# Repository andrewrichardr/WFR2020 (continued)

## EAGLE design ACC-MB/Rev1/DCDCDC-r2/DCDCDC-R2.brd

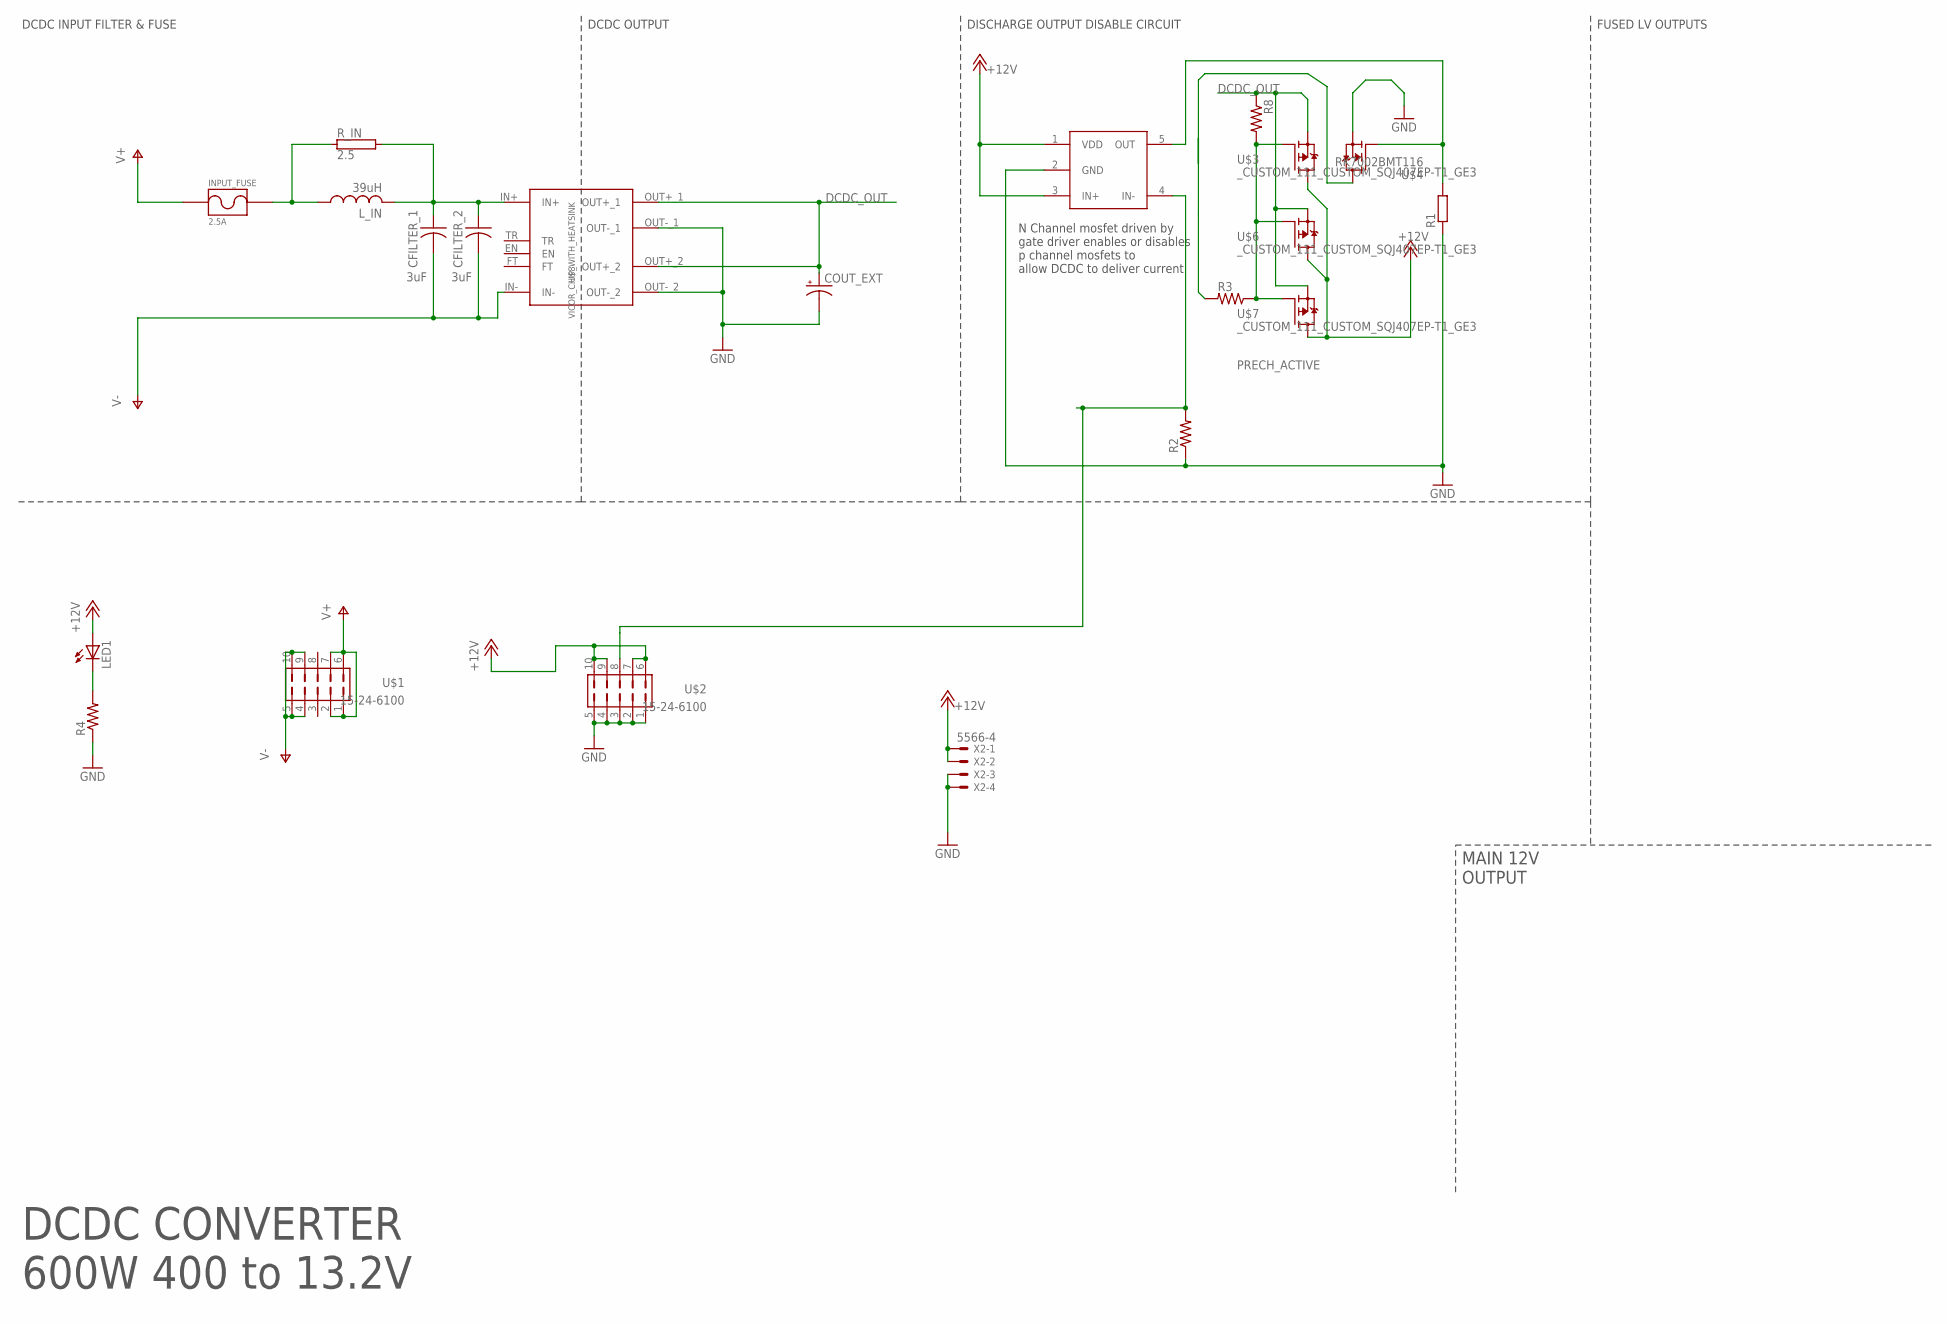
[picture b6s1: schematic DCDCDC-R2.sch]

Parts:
CFILTER_1, CFILTER_2: 3uF; CERALINK_FA3
COUT_EXT: CPOL-USE7.5-16; E7,5-16
INPUT_FUSE: 2.5A; _CUSTOM_PARTS_LF_885
LED1: LED3MM
L_IN: 39uH; L_1510_NONSTANDARD
R1: R-EU_R0805; R0805
R2, R3, R4, R8: R-US_R0805; R0805
R_IN: 2.5; TO-247-2V
U$1, U$2: 15-24-6100
U$3, U$6, U$7: _CUSTOM_111_CUSTOM_SQJ407EP-T1_GE3; _CUSTOM_111_CUSTOM_TRANS_SIRA90DP-T1-GE3
U$4: RK7002BMT116; SOT23
U$5: UCC27511AQDBVRQ1; SOT23-5L
U$8: VICOR_CHIP_WITH_HEATSINK; VICOR_CHIP_HEATSINK
X2: 5566-4

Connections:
+12V: LED1.A, U$2.6, U$2.7, U$2.9, U$2.10, U$3.5 (D), U$5.1 (VDD), U$5.3 (IN+), U$6.5 (D), U$7.5 (D), X2.1, X2.2
DCDC_OUT: COUT_EXT.+, R8.1, U$3.1 (S), U$3.2 (S), U$3.3 (S), U$6.1 (S), U$6.2 (S), U$6.3 (S), U$7.1 (S), U$7.2 (S), U$7.3 (S), U$8.OUT+_1, U$8.OUT+_2
GND: COUT_EXT.-, R1.1, R2.1, R4.1, U$2.1, U$2.2, U$2.3, U$2.4, U$2.5, U$4.2 (S), U$5.2 (GND), U$8.OUT-_1, U$8.OUT-_2, X2.3, X2.4
unnamed: R3.1, R8.2, U$3.4 (G), U$6.4 (G), U$7.4 (G)
unnamed: R1.2, U$4.1 (G), U$5.5 (OUT)
unnamed: CFILTER_1.P$1 (1), CFILTER_2.P$1 (1), L_IN.P$2 (2), R_IN.2, U$8.IN+
unnamed: R3.2, U$4.3 (D)
unnamed: LED1.K (C), R4.2
PRECH_ACTIVE: R2.2, U$2.8, U$5.4 (IN-)
V+: INPUT_FUSE.P$1, U$1.1, U$1.2, U$1.6, U$1.7
V+_FUSED: INPUT_FUSE.P$2, L_IN.P$1 (1), R_IN.1
V-: CFILTER_1.P$2 (2), CFILTER_2.P$2 (2), U$1.4, U$1.5, U$1.9, U$1.10, U$8.IN-

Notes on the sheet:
DCDC CONVERTER 600W 400 to 13.2V
DISCHARGE OUTPUT DISABLE CIRCUIT
FUSED LV OUTPUTS
MAIN 12V OUTPUT
DCDC OUTPUT
DCDC INPUT FILTER & FUSE
N Channel mosfet driven by gate driver enables or disables p channel mosfets to allow DCDC to deliver current

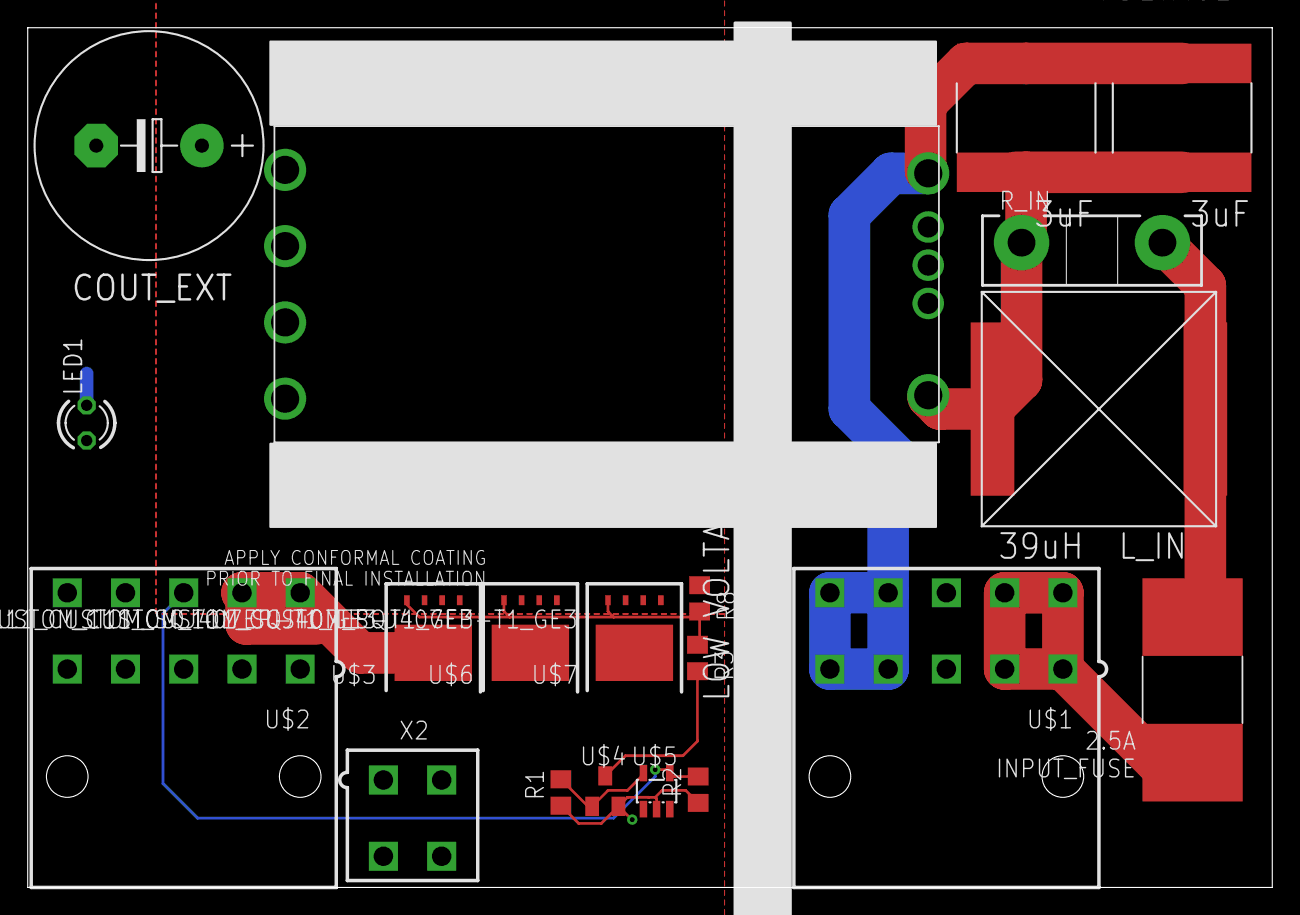
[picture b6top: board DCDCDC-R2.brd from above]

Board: 2 copper layers, 89.8 x 62.0 mm, 23 parts (1 on the bottom side), 12 nets.

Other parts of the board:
U$9, U$10: 7792

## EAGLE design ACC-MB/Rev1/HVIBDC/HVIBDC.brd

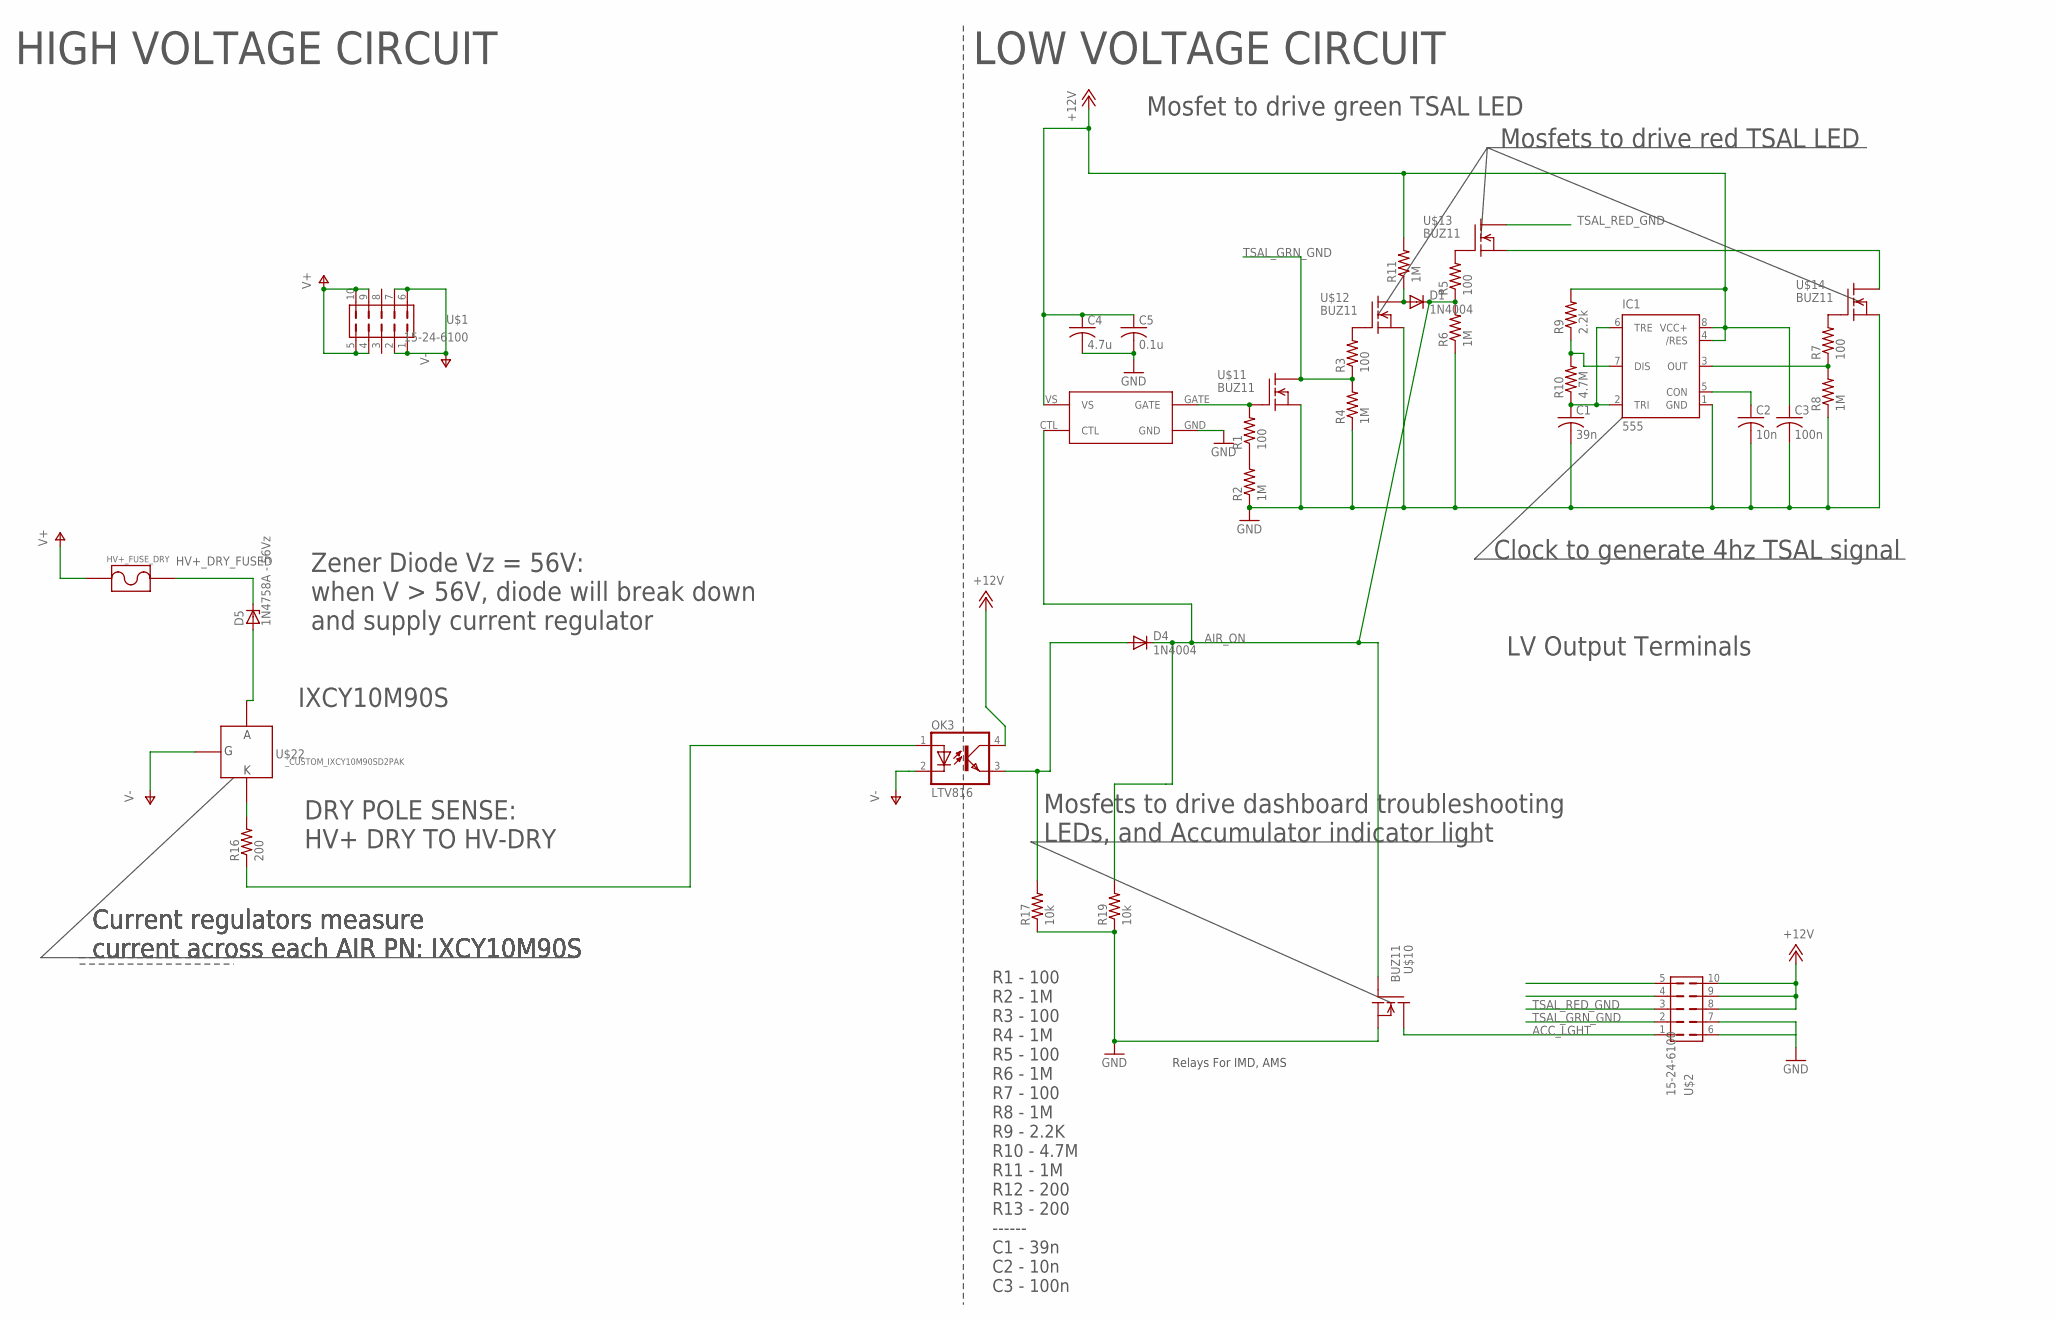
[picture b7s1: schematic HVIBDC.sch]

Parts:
C1: 39n; C0805
C2: 10n; C0805
C3: 100n; C0805
C4: 4.7u; C0805
C5: 0.1u; C0805
D1, D4: 1N4004; DO41-10
D5: 1N4758A - 56Vz; ZDIO12.5
HV+_FUSE_DRY: _CUSTOM_PARTS_LF_885
IC1: 555; DIP08
OK3: LTV816; DIL04
R1, R3, R5, R7: 100; R0805
R2, R4, R6, R8, R11: 1M; R0805
R9: 2.2k; R0805
R10: 4.7M; R0805
R16: 200; R2010
R17, R19: 10k; R0805
U$1, U$2: 15-24-6100
U$10, U$11, U$12, U$13, U$14: BUZ11; TO220
U$15: MIC4417; PDM_2019_REVB_MIC4416YM4-TR
U$22: _CUSTOM_IXCY10M90SD2PAK; TO228P991X238-3

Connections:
+12V: C3.1, C4.1, C5.1, IC1.4 (/RES), IC1.8 (VCC+), OK3.4 (COL), R9.2, R11.2, U$2.8, U$2.9, U$2.10, U$15.VS
ACC_LGHT: U$2.1, U$10.2 (D)
AIR_ON: D1.C, D4.C, R5.1, R6.2, R19.2, U$10.1 (G), U$15.CTL
GND: C1.2, C2.2, C3.2, C4.2, C5.2, IC1.1 (GND), R2.1, R4.1, R6.1, R8.1, R17.1, R19.1, U$2.7, U$10.3 (S), U$11.3 (S), U$12.3 (S), U$14.3 (S), U$15.GND
HV+_DRY_FUSED: D5.C, HV+_FUSE_DRY.P$1
unnamed: R1.1, R2.2
unnamed: R1.2, U$11.1 (G), U$15.GATE
unnamed: R3.2, U$12.1 (G)
unnamed: C2.1, IC1.5 (CON)
unnamed: IC1.7 (DIS), R9.1, R10.2
unnamed: R5.2, U$13.1 (G)
unnamed: R7.2, U$14.1 (G)
unnamed: IC1.3 (OUT), R7.1, R8.2
unnamed: C1.1, IC1.2 (TRI), IC1.6 (TRE), R10.1
unnamed: U$13.3 (S), U$14.2 (D)
unnamed: D4.A, OK3.3 (EMIT), R17.2
unnamed: D1.A, R11.1, U$12.2 (D)
unnamed: R16.2, U$22.2 (K)
unnamed: D5.A, U$22.3 (A)
unnamed: OK3.1 (A), R16.1
TSAL_GRN_GND: R3.1, R4.2, U$2.2, U$11.2 (D)
TSAL_RED_GND: U$2.3, U$13.2 (D)
V+: HV+_FUSE_DRY.P$2, U$1.4, U$1.5, U$1.9, U$1.10
V-: OK3.2 (C), U$1.1, U$1.2, U$1.6, U$1.7, U$22.1 (G)

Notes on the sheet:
HIGH VOLTAGE CIRCUIT
LOW VOLTAGE CIRCUIT
Mosfets to drive dashboard troubleshooting LEDs, and Accumulator indicator light
Clock to generate 4hz TSAL signal
Mosfets to drive red TSAL LED
Mosfet to drive green TSAL LED
LV Output Terminals
R1 - 100 R2 - 1M R3 - 100 R4 - 1M R5 - 100 R6 - 1M R7 - 100 R8 - 1M R9 - 2.2K R10 - 4.7M R11 - 1M R12 - 200 R13 - 200 ------ C1 - 39n C2 - 10n C3 - 100n
Relays For IMD, AMS
Current regulators measure current across each AIR PN: IXCY10M90S
DRY POLE SENSE: HV+ DRY TO HV-DRY
IXCY10M90S
Zener Diode Vz = 56V: when V > 56V, diode will break down and supply current regulator

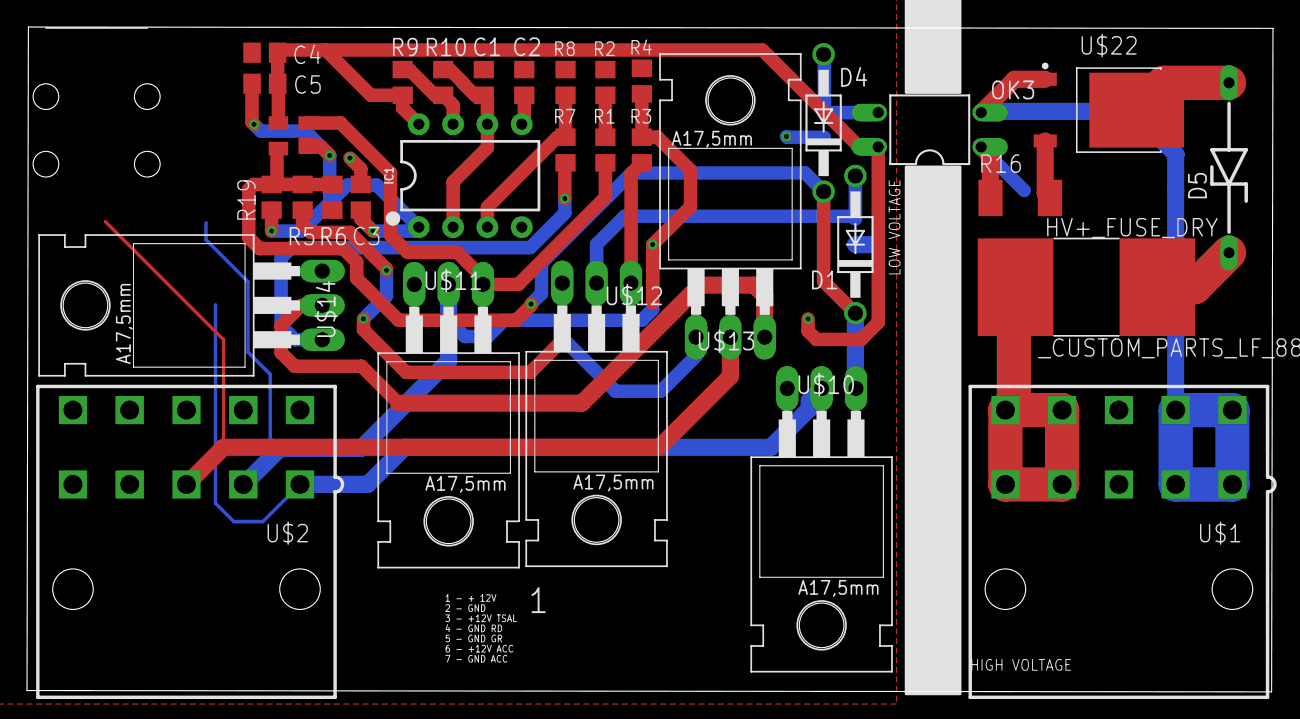
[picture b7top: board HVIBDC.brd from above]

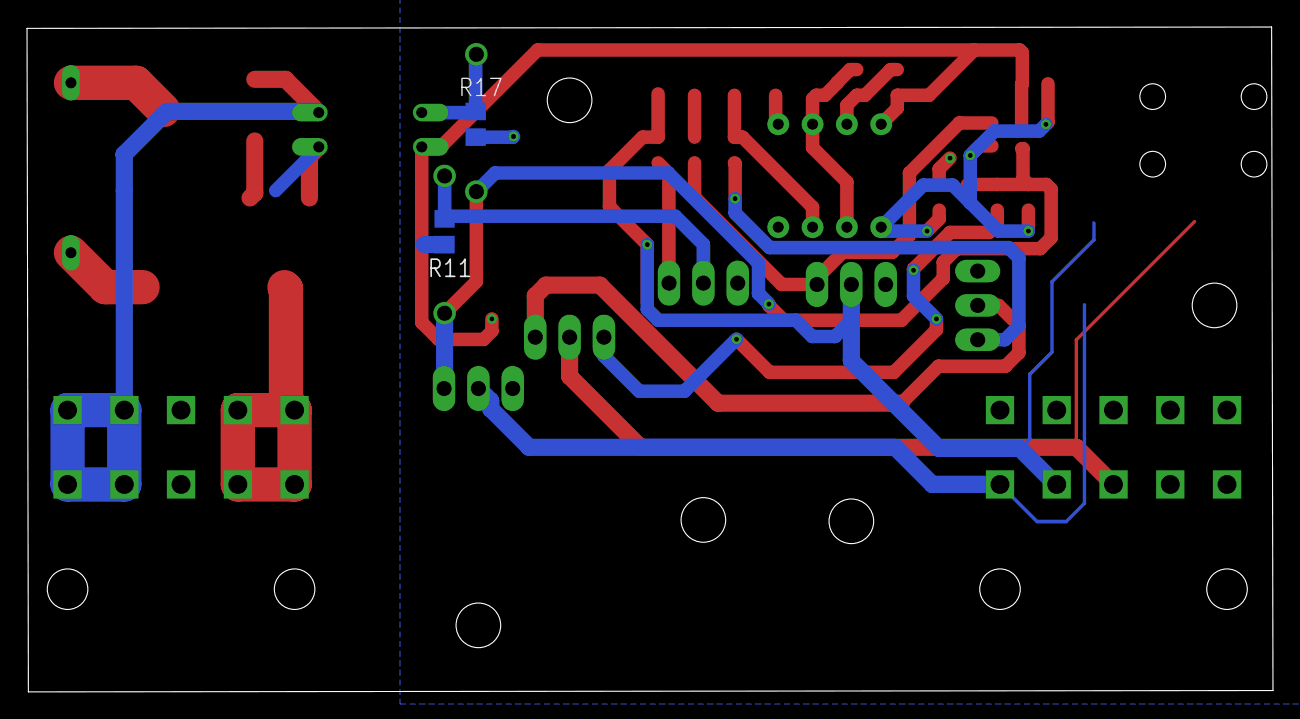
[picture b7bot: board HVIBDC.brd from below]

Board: 2 copper layers, 92.2 x 49.2 mm, 36 parts (2 on the bottom side), 24 nets.

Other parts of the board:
U$3, U$4: 7792
